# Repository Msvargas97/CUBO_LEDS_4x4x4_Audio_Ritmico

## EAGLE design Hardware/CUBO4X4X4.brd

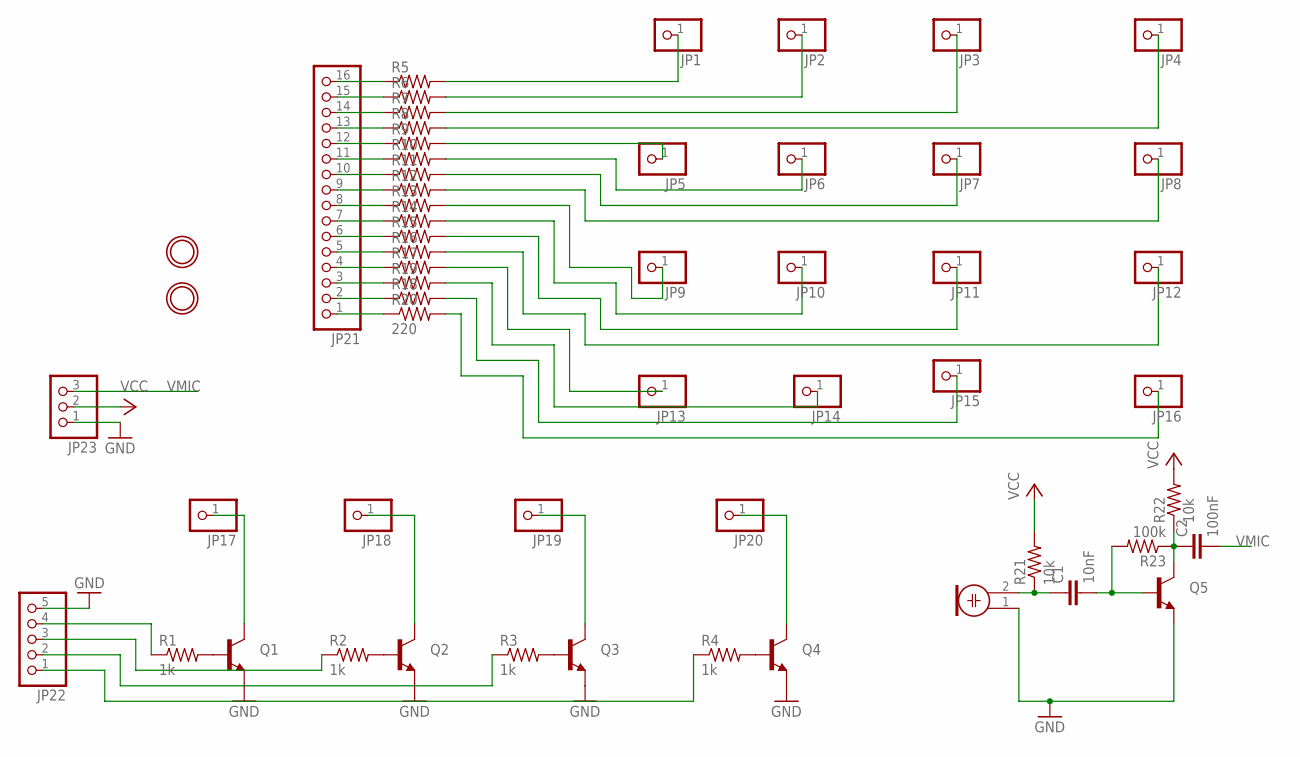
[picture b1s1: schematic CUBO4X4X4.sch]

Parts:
C1: 10nF; C2.5-2
C2: 100nF; C2.5-2
JP1, JP2, JP3, JP4, JP5, JP6, JP7, JP8, JP9, JP10, JP11, JP12, JP13, JP14, JP15, JP16, JP17, JP18, JP19, JP20: PINHD-1X1; 1X01
JP21: PINHD-1X16; 1X16
JP22: PINHD-1X5; 1X05
JP23: PINHD-1X3; 1X03
M1: ELECTRET_MICROPHON-WM.64PN; WM-64PN
Q1, Q2, Q3, Q4, Q5: TRANSISTOR_NPNTO-92-AMMO; TO-92-AMMO
R1, R2, R3, R4: 1k; 0207/10
R5, R6, R7, R8, R9, R10, R11, R12, R13, R14, R15, R16, R17, R18, R19: R-US_0207/10; 0207/10
R20: 220; 0207/10
R21, R22: 10k; 0207/10
R23: 100k; 0207/10
U$7, U$8: MOUNTINGHOLE2.5_THICK; MOUNTINGHOLE_2.5_PLATED_THICK

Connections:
GND: JP22.5, JP23.1, M1.1, Q1.1 (E), Q2.1 (E), Q3.1 (E), Q4.1 (E), Q5.1 (E)
unnamed: JP17.1, Q1.3 (C)
unnamed: JP18.1, Q2.3 (C)
unnamed: JP19.1, Q3.3 (C)
unnamed: Q1.2 (B), R1.2
unnamed: Q2.2 (B), R2.2
unnamed: Q3.2 (B), R3.2
unnamed: Q4.2 (B), R4.2
unnamed: JP20.1, Q4.3 (C)
unnamed: JP21.16, R5.1
unnamed: JP21.15, R6.1
unnamed: JP21.14, R7.1
unnamed: JP21.13, R8.1
unnamed: JP21.12, R9.1
unnamed: JP21.11, R10.1
unnamed: JP21.10, R11.1
unnamed: JP21.9, R12.1
unnamed: JP21.8, R13.1
unnamed: JP21.7, R14.1
unnamed: JP21.6, R15.1
unnamed: JP21.5, R16.1
unnamed: JP21.4, R17.1
unnamed: JP21.3, R19.1
unnamed: JP21.2, R18.1
unnamed: JP21.1, R20.1
unnamed: JP1.1, R5.2
unnamed: JP2.1, R6.2
unnamed: JP3.1, R7.2
unnamed: JP4.1, R8.2
unnamed: JP5.1, R9.2
unnamed: JP6.1, R10.2
unnamed: JP7.1, R11.2
unnamed: JP8.1, R12.2
unnamed: JP9.1, R13.2
unnamed: JP10.1, R14.2
unnamed: JP11.1, R15.2
unnamed: JP12.1, R16.2
unnamed: JP13.1, R17.2
unnamed: JP14.1, R19.2
unnamed: JP15.1, R18.2
unnamed: JP16.1, R20.2
unnamed: JP22.4, R1.1
unnamed: JP22.3, R2.1
unnamed: JP22.2, R3.1
unnamed: JP22.1, R4.1
unnamed: C1.1, M1.2, R21.1
unnamed: C1.2, Q5.2 (B), R23.2
VCC: JP23.2, R21.2, R22.2
VMIC: C2.1, C2.2, JP23.3, Q5.3 (C), R22.1, R23.1

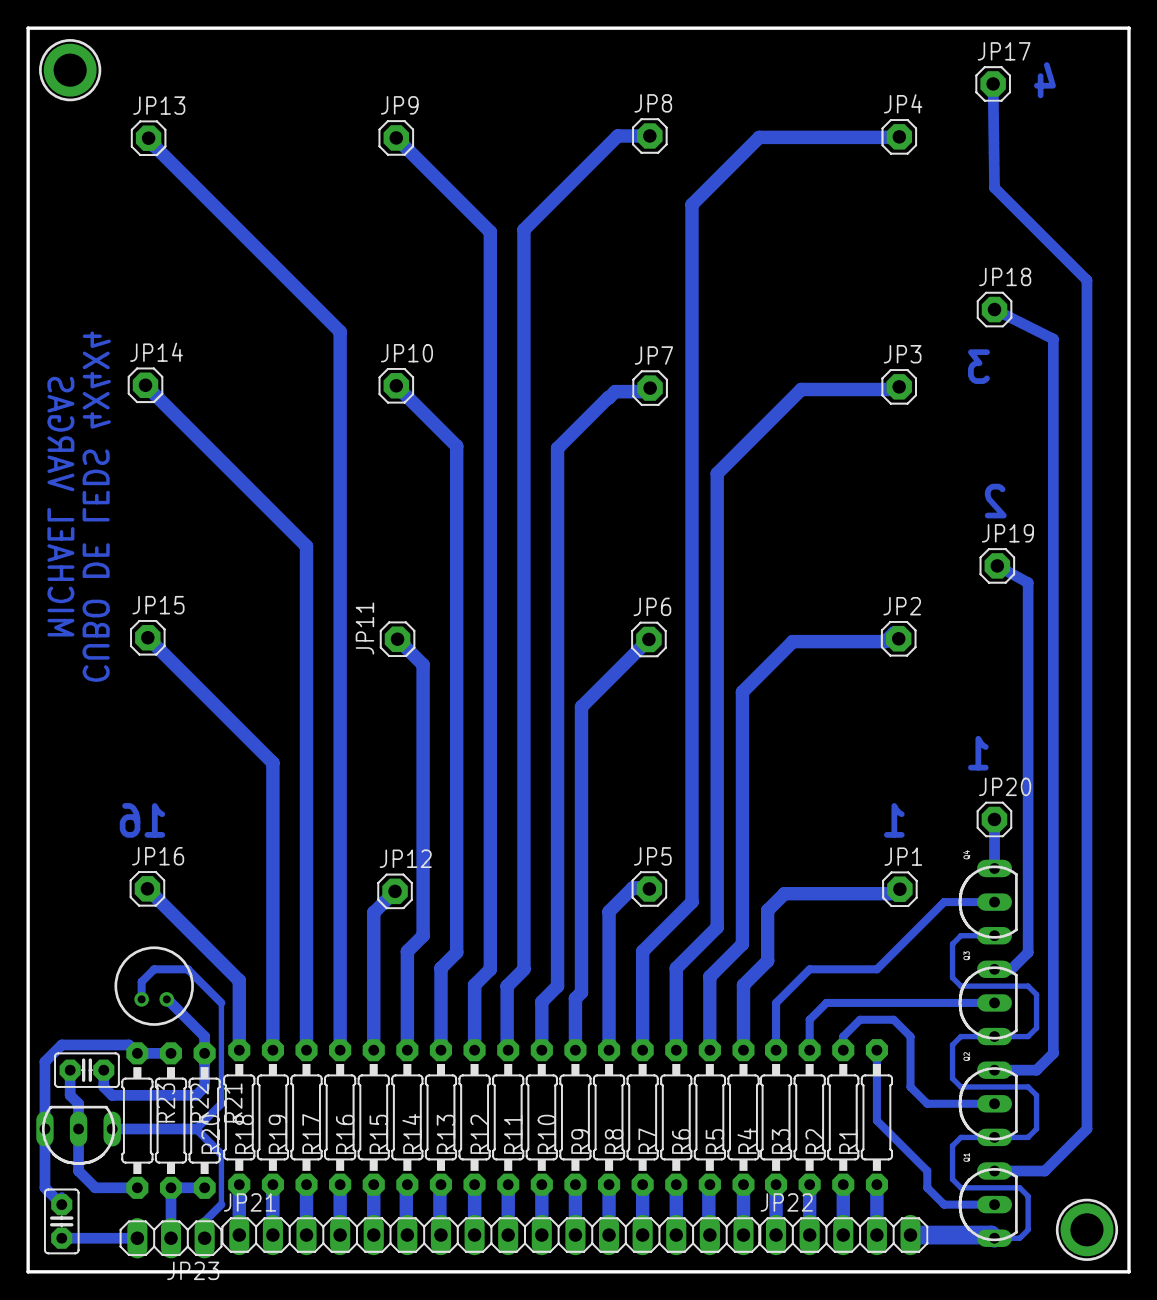
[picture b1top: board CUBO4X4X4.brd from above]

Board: 2 copper layers, 83.2 x 94.0 mm, 56 parts (0 on the bottom side), 49 nets.

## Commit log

2015-12-07 :neckbeard: Added .gitattributes & .gitignore files
2015-12-07 Cubo de LEDS con PIC
    Init

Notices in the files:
parts and their libraries:
SparkFun-DiscreteSemi: Licensing: Creative Commons ShareAlike 4.0 International - https://creativecommons.org/licenses/by-sa/4.0
microbuilder: This work is placed in the public domain, and may be freely used for commercial and non-commercial work with the following conditions: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
